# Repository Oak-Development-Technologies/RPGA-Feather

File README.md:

<image src="/images/RPGA_Feather_Banner.jpeg">

# RPGA-Feather

Welcome to the RPGA Feather GitHub page. This page is designed to be a single source of truth for this board, including board files like schematics, production files, BOM, and more. In addition to that, there are also a handful of examples available to build with just a little effort specifically for the RPGA Feather.

Continue reading to get started.

# Getting Started

What is the RPGA Feather? RPGA Feather is a development board which provides the ease of use of the RP2040 from Raspberry Pi with the wide open source support of the iCE40 FPGA line. RPGA Feather combines the RP2040 with an iCE5LP4K FPGA from Lattice Semiconductor which has 3520 LUTs, 2 hardware SPI and I2C blocks, a bright RGB LED driver, two internal oscillators, and 1 PLL which can be used to generate additional clocks for your designs.

RPGA Feather provides up to 11 direct GPIO connected between the RP2040 and the iCE5LP4K. This includes the 3 pins used for programming the bitstream onto the FPGA.

Having a good pinout guide can be useful for getting started. We provide this pinout card with every RPGA Feather purchased from our shop.

<image src="/images/RPGA%20Feather%20rev%20b.jpg">

You can find the PDF under the [Hardware Directory Here](/hardware/RPGA.pdf). Thanks to [@skliffmueller](https://github.com/skliffmueller) for making and sharing it.

### usage examples

We provide a few examples in this repository for getting familiar with interfacing with the iCE5LP4K FPGA.

Following the comments in the [top.v](/src/top.v) file under the `src` directory can enable you to build these specific examples quickly. Once you have the example set up in the file, you can build it using the following command:

```make
make build
```

Building requires using Yosys OSS CAD Suite, which can be found by visiting the [OSS CAD Suite build github repository](https://github.com/YosysHQ/oss-cad-suite-build). Follow the instructions for setting up the tools on your OS and you'll be good to go.

Once you have a `top.bin` file which should be in the base directory of the repository, you can simply copy it over onto your RPGA Feather `CIRCUITPY` drive. If you haven't downloaded the CircuitPython Community Bundle to get IcePython you can [head to the CircuitPython Libraries page](https://circuitpython.org/libraries) to download it, or [download the latest release directly](https://github.com/skerr92/Oakdevtech_CircuitPython_IcePython/releases).

Once you have IcePython and the `top.bin` file loaded onto your RPGA Feather, the next step is to get your code setup to load the FPGA.

Using Mu or your favorite CircuitPython compatible IDE, open up the `code.py` file and past the following code:

```py
# SPDX-FileCopyrightText: 2017 Scott Shawcroft, written for Adafruit Industries
# SPDX-FileCopyrightText: Copyright (c) 2023 Seth Kerr for Oak Development Technologies
#
# SPDX-License-Identifier: Unlicense

"""
Example showing how to program an iCE40 FPGA with circuitpython!
"""

import time
import board, busio
import oakdevtech_icepython
import gc

print("Mem Free: ",gc.mem_free(),"Mem Alloc", gc.mem_alloc())
spi = busio.SPI(clock=board.F_SCK, MOSI=board.F_MOSI, MISO=board.F_MISO)

iceprog = oakdevtech_icepython.Oakdevtech_icepython(
    spi, board.F_CSN, board.F_RST, "top.bin"
)

timestamp = time.monotonic()

iceprog.program_fpga()

endstamp = time.monotonic()
print("done in: ", (endstamp - timestamp), "seconds")

print("done")
```
Save the file and you should see the green CDONE LED light up on your board. Depending on the example you built, you might see the RGB LED light up that is next to the FPGA.

### Questions?

If you have any questions, please feel free to open an issue. Issues are a great way to raise concerns or bugs with the examples or hardware itself. And your feedback is critical to making sure we can fix issues and improve the quality of life for everyone's experience with RPGA Feather.

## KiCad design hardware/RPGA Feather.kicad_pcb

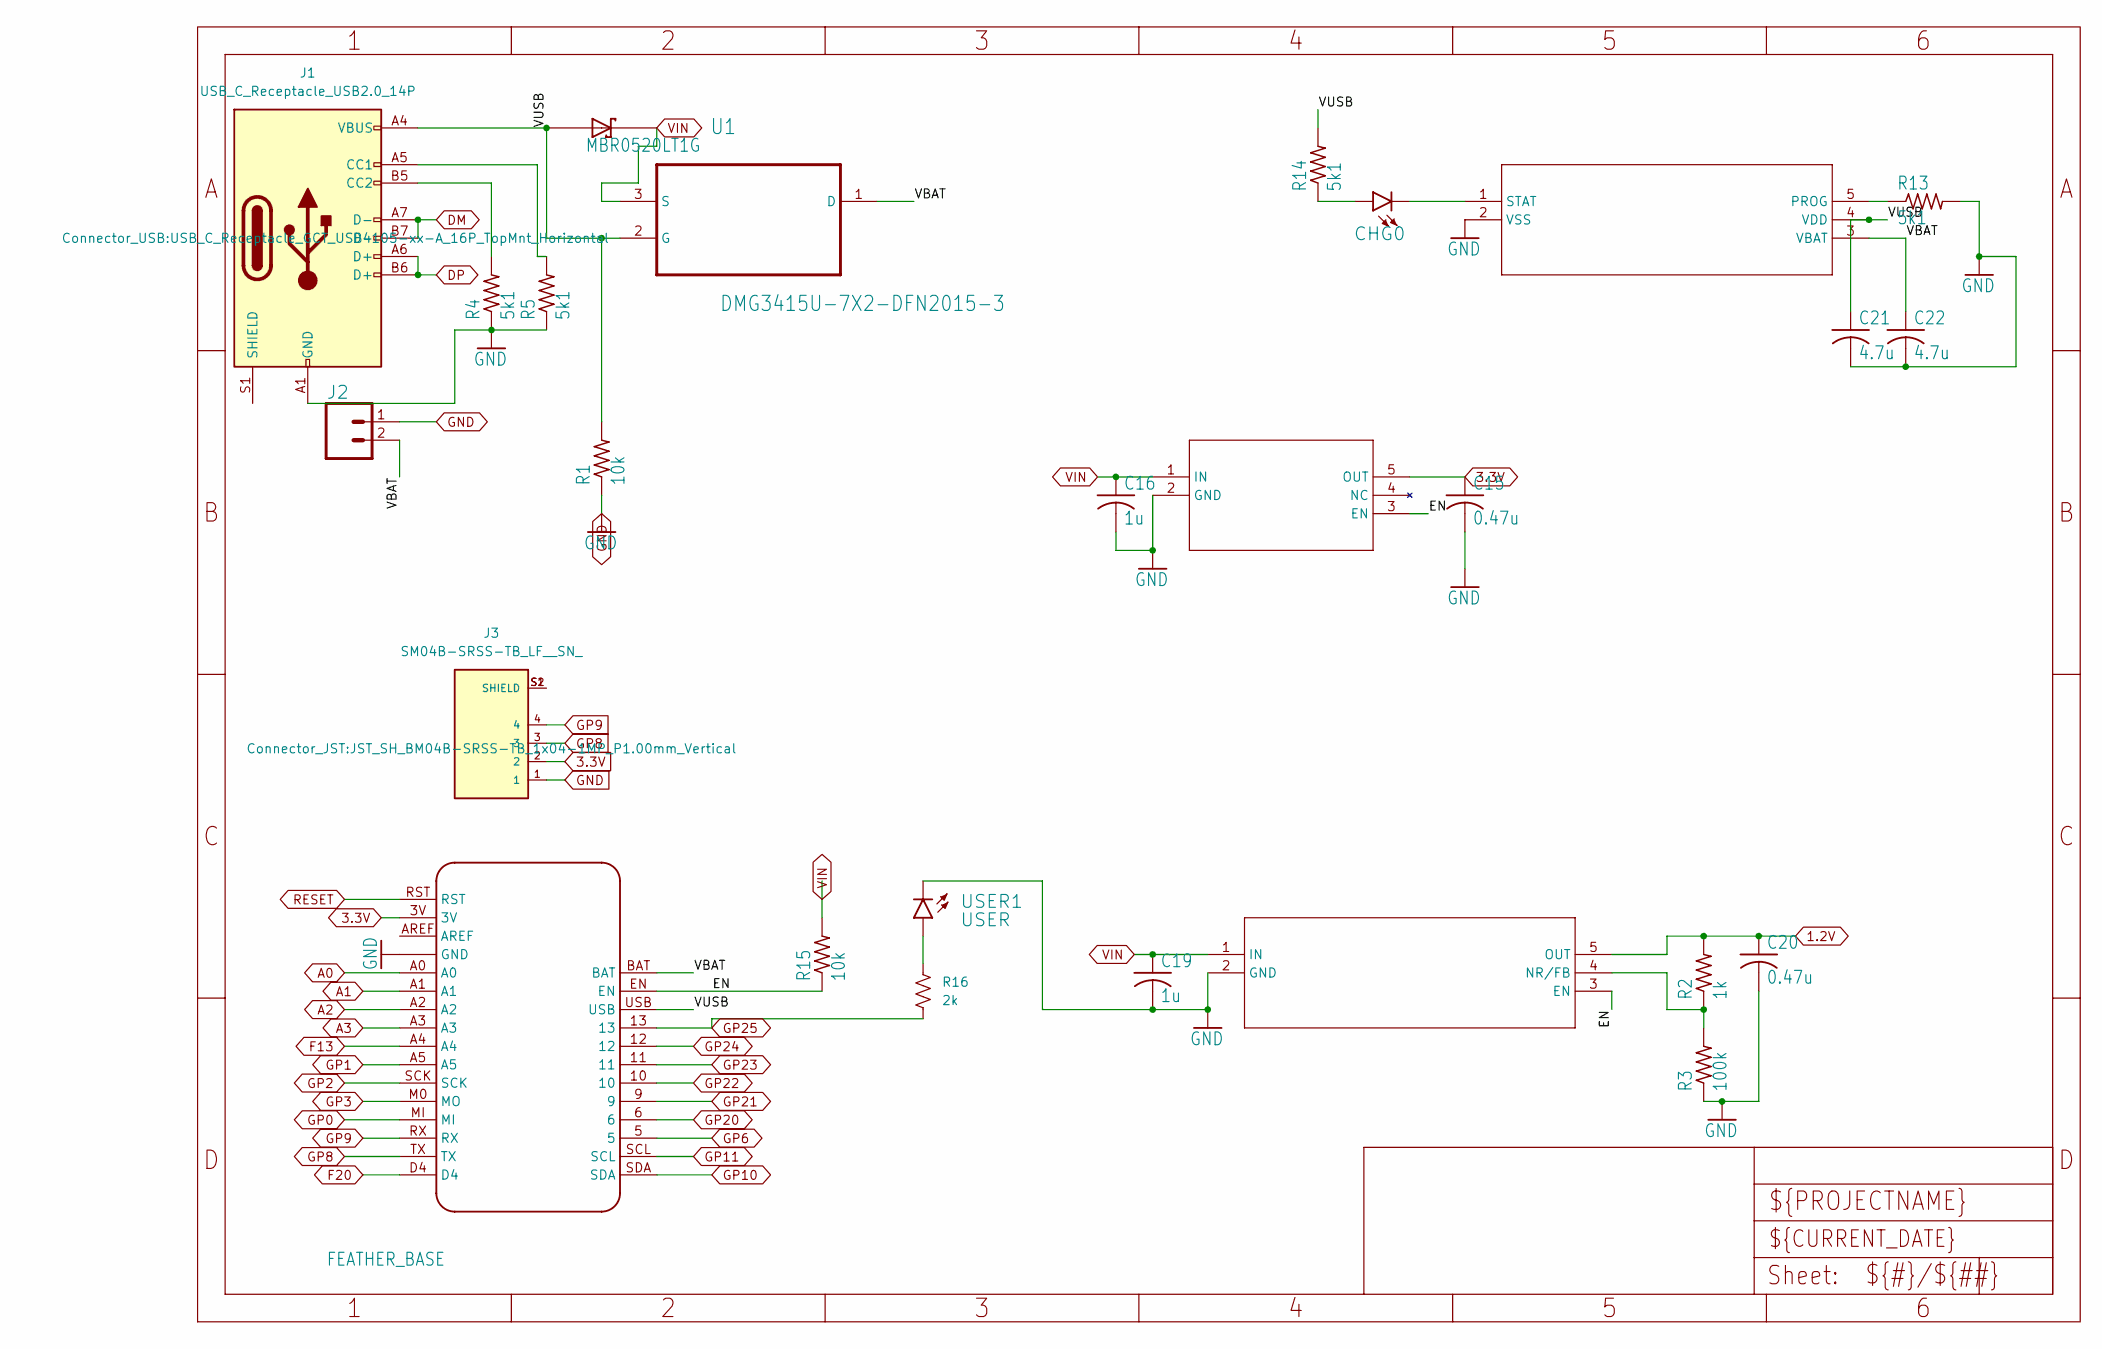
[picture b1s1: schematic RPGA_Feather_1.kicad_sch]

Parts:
C15, C20: 0.47u; C_0402_1005Metric
C16, C19: 1u; C_0402_1005Metric
C21, C22: 4.7u; C_0603_1608Metric
CHG0: LED0603; LED-0603
J1: USB_C_Receptacle_USB2.0_14P; USB_C_Receptacle_GCT_USB4105-xx-A_16P_TopMnt_Horizontal
J2: CONN_02-JST-2MM-SMT; JST-2-SMD
J3: SM04B-SRSS-TB_LF__SN_; JST_SH_BM04B-SRSS-TB_1x04-1MP_P1.00mm_Vertical
R1, R15: 10k; R0402
R2: 1k; R0402
R3: 100k; R0402
R4, R5, R13, R14: 5k1; R0402
R16: 2k; R_0402_1005Metric
U1: DMG3415U-7X2-DFN2015-3; X2-DFN2015-3
U2: MCP73831T-2ACI/OTSOT-23-5_MC-L; SOT-23-5_MC-L
U3: TPS73201DBVRDBV5-L; DBV5-L
U4: TLV75533PDBVRDBV5_TEX-L; DBV5_TEX-L
U$1: FEATHER_BASE; FEATHER_PINS
U$2: MBR0520LT1G; SOD3716X117(SOD-123)
USER1: USER; LED-0603

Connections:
1.2V: C20.1, R2.2, U3.5 (OUT); also elsewhere on the board
3.3V: C15.1, J3.2, U4.5 (OUT), U$1.3V; also elsewhere on the board
/RPGA Feather_1/EN: R15.1, U3.3 (EN), U4.3 (EN), U$1.EN
/RPGA Feather_1/VBAT: C22.1, J2.2 (1), U1.1 (D), U2.3 (VBAT), U$1.BAT
/RPGA Feather_1/VUSB: C21.1, J1.A4 (VBUS), J1.A9 (VBUS), J1.B4 (VBUS), J1.B9 (VBUS), R1.2, R14.2, U1.2 (G), U2.4 (VDD), U$1.USB, U$2.2 (A)
A0: U$1.A0; also elsewhere on the board
A1: U$1.A1; also elsewhere on the board
A2: U$1.A2; also elsewhere on the board
A3: U$1.A3; also elsewhere on the board
DM: J1.A7 (D-), J1.B7 (D-); also elsewhere on the board
DP: J1.A6 (D+), J1.B6 (D+); also elsewhere on the board
F13: U$1.A4; also elsewhere on the board
F20: U$1.D4; also elsewhere on the board
GND: C15.2, C16.2, C19.2, C20.2, C21.2, C22.2, J1.A1 (GND), J1.A12 (GND), J1.B1 (GND), J1.B12 (GND), J2.1 (2), J3.1, R1.1, R3.1, R4.1, R5.1, R13.2, U2.2 (VSS), U3.2 (GND), U4.2 (GND), U$1.GND, U$1.P$1 (GND), U$1.P$2 (GND), USER1.C; also elsewhere on the board
GP0: U$1.MI; also elsewhere on the board
GP1: U$1.A5; also elsewhere on the board
GP2: U$1.SCK; also elsewhere on the board
GP3: U$1.M0 (MO); also elsewhere on the board
GP6: U$1.5; also elsewhere on the board
GP8: J3.3, U$1.TX; also elsewhere on the board
GP9: J3.4, U$1.RX; also elsewhere on the board
GP10: U$1.SDA; also elsewhere on the board
GP11: U$1.SCL; also elsewhere on the board
GP20: U$1.6; also elsewhere on the board
GP21: U$1.9; also elsewhere on the board
GP22: U$1.10; also elsewhere on the board
GP23: U$1.11; also elsewhere on the board
GP24: U$1.12; also elsewhere on the board
GP25: R16.2, U$1.13; also elsewhere on the board
unnamed: CHG0.A, R14.1
unnamed: J1.A5 (CC1), R5.2
unnamed: J1.B5 (CC2), R4.2
unnamed: R16.1, USER1.A
unnamed: R13.1, U2.5 (PROG)
unnamed: CHG0.C, U2.1 (STAT)
unnamed: R2.1, R3.2, U3.4 (NR/FB)
RESET: U$1.RST; also elsewhere on the board
VIN: C16.1, C19.1, R15.2, U1.3 (S), U3.1 (IN), U4.1 (IN), U$2.1 (C)

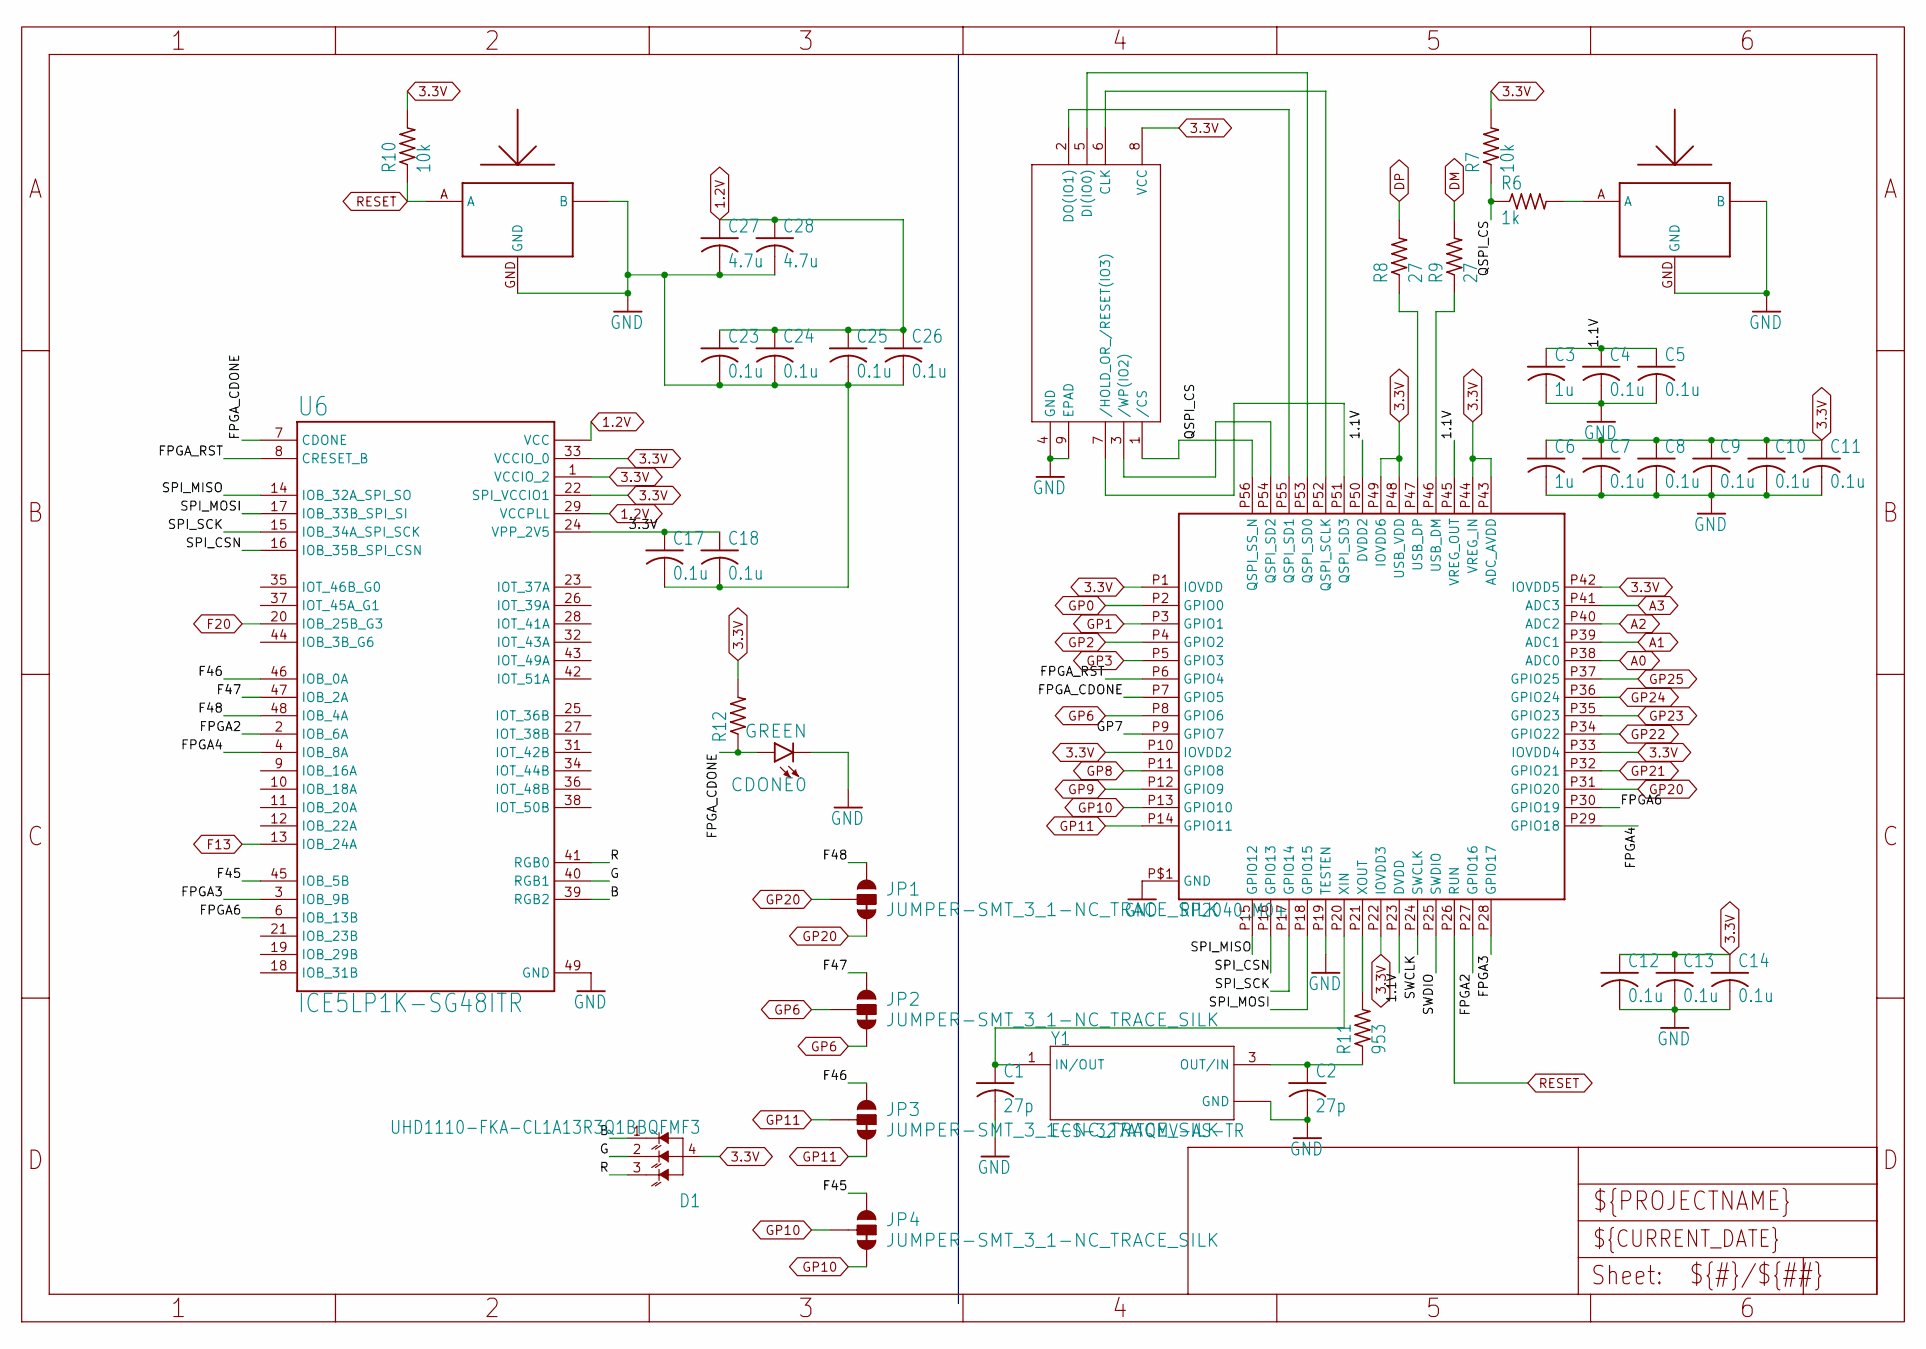
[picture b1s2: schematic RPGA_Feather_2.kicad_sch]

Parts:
C1, C2: 27p; C_0402_1005Metric
C3, C6: 1u; C_0402_1005Metric
C4, C5, C7, C8, C9, C10, C11, C12, C13, C14, C17, C18, C23, C24, C25, C26: 0.1u; C_0402_1005Metric
C27, C28: 4.7u; C_0603_1608Metric
CDONE0: GREEN; LED-0603
D1: UHD1110-FKA-CL1A13R3Q1BBQFMF3; LED_UHD1110-FKA-CL1A13R3Q1BBQFMF3
JP1, JP2, JP3, JP4: JUMPER-SMT_3_1-NC_TRACE_SILK; SMT-JUMPER_3_1-NC_TRACE_SILK
R6: 1k; R0402
R7, R10: 10k; R0402
R8, R9: 27; R0402
R11: 953; R0402
R12: R-US_R0402; R0402
U6: ICE5LP1K-SG48ITR; QFN50P700X700X100-49N
U7: W25Q16JVUXIQW25Q16JVUXIQ_WIN-L; W25Q16JVUXIQ_WIN-L
U$3: RP2040_M0+; QFN-56
U$4, U$5: SOF-232HST; 3.3X2.9
Y1: ECS-327ATQMV-AS-TR; XTAL_ECS-327ATQMV-AS-TR

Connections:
1.2V: C23.1, C24.1, C25.1, C26.1, C27.1, C28.1, U6.5 (VCC), U6.29 (VCCPLL), U6.30 (VCC); also elsewhere on the board
3.3V: C6.1, C7.1, C8.1, C9.1, C10.1, C11.1, C12.1, C13.1, C14.1, C17.1, C18.1, D1.4 (ANODE), R7.2, R10.2, R12.2, U6.1 (VCCIO_2), U6.22 (SPI_VCCIO1), U6.24 (VPP_2V5), U6.33 (VCCIO_0), U7.8 (VCC), U$3.P1 (IOVDD), U$3.P10 (IOVDD2), U$3.P22 (IOVDD3), U$3.P33 (IOVDD4), U$3.P42 (IOVDD5), U$3.P43 (ADC_AVDD), U$3.P44 (VREG_IN), U$3.P48 (USB_VDD), U$3.P49 (IOVDD6); also elsewhere on the board
/RPGA Feather_2/1.1V: C3.1, C4.1, C5.1, U$3.P23 (DVDD), U$3.P45 (VREG_OUT), U$3.P50 (DVDD2)
/RPGA Feather_2/B: D1.1 (BLUE), U6.39 (RGB2)
/RPGA Feather_2/F45: JP4.1, U6.45 (IOB_5B)
/RPGA Feather_2/F46: JP3.1, U6.46 (IOB_0A)
/RPGA Feather_2/F47: JP2.1, U6.47 (IOB_2A)
/RPGA Feather_2/F48: JP1.1, U6.48 (IOB_4A)
/RPGA Feather_2/FPGA2: U6.2 (IOB_6A), U$3.P27 (GPIO16)
/RPGA Feather_2/FPGA3: U6.3 (IOB_9B), U$3.P28 (GPIO17)
/RPGA Feather_2/FPGA4: U6.4 (IOB_8A), U$3.P29 (GPIO18)
/RPGA Feather_2/FPGA6: U6.6 (IOB_13B), U$3.P30 (GPIO19)
/RPGA Feather_2/FPGA_CDONE: CDONE0.A, R12.1, U6.7 (CDONE), U$3.P7 (GPIO5)
/RPGA Feather_2/FPGA_RST: U6.8 (CRESET_B), U$3.P6 (GPIO4)
/RPGA Feather_2/G: D1.2 (GREEN), U6.40 (RGB1)
/RPGA Feather_2/GP7: U$3.P9 (GPIO7)
/RPGA Feather_2/QSPI_CS: R6.1, R7.1, U7.1 (/CS), U$3.P56 (QSPI_SS_N)
/RPGA Feather_2/R: D1.3 (RED), U6.41 (RGB0)
/RPGA Feather_2/SPI_CSN: U6.16 (IOB_35B_SPI_CSN), U$3.P16 (GPIO13)
/RPGA Feather_2/SPI_MISO: U6.14 (IOB_32A_SPI_SO), U$3.P15 (GPIO12)
/RPGA Feather_2/SPI_MOSI: U6.17 (IOB_33B_SPI_SI), U$3.P18 (GPIO15)
/RPGA Feather_2/SPI_SCK: U6.15 (IOB_34A_SPI_SCK), U$3.P17 (GPIO14)
/RPGA Feather_2/SWCLK: U$3.P24 (SWCLK)
/RPGA Feather_2/SWDIO: U$3.P25 (SWDIO)
A0: U$3.P38 (ADC0); also elsewhere on the board
A1: U$3.P39 (ADC1); also elsewhere on the board
A2: U$3.P40 (ADC2); also elsewhere on the board
A3: U$3.P41 (ADC3); also elsewhere on the board
DM: R9.2; also elsewhere on the board
DP: R8.2; also elsewhere on the board
F13: U6.13 (IOB_24A); also elsewhere on the board
F20: U6.20 (IOB_25B_G3); also elsewhere on the board
GND: C1.2, C2.2, C3.2, C4.2, C5.2, C6.2, C7.2, C8.2, C9.2, C10.2, C11.2, C12.2, C13.2, C14.2, C17.2, C18.2, C23.2, C24.2, C25.2, C26.2, C27.2, C28.2, CDONE0.C, U6.49 (GND), U7.4 (GND), U7.9 (EPAD), U$3.P19 (TESTEN), U$3.P$1 (GND), U$4.B, U$4.B2 (B), U$4.B3 (B), U$4.GND, U$5.B, U$5.B2 (B), U$5.B3 (B), U$5.GND, Y1.2 (GND), Y1.4 (GND); also elsewhere on the board
GP0: U$3.P2 (GPIO0); also elsewhere on the board
GP1: U$3.P3 (GPIO1); also elsewhere on the board
GP2: U$3.P4 (GPIO2); also elsewhere on the board
GP3: U$3.P5 (GPIO3); also elsewhere on the board
GP6: JP2.2, JP2.3, U$3.P8 (GPIO6); also elsewhere on the board
GP8: U$3.P11 (GPIO8); also elsewhere on the board
GP9: U$3.P12 (GPIO9); also elsewhere on the board
GP10: JP4.2, JP4.3, U$3.P13 (GPIO10); also elsewhere on the board
GP11: JP3.2, JP3.3, U$3.P14 (GPIO11); also elsewhere on the board
GP20: JP1.2, JP1.3, U$3.P31 (GPIO20); also elsewhere on the board
GP21: U$3.P32 (GPIO21); also elsewhere on the board
GP22: U$3.P34 (GPIO22); also elsewhere on the board
GP23: U$3.P35 (GPIO23); also elsewhere on the board
GP24: U$3.P36 (GPIO24); also elsewhere on the board
GP25: U$3.P37 (GPIO25); also elsewhere on the board
unnamed: R6.2, U$5.A
unnamed: U7.6 (CLK), U$3.P52 (QSPI_SCLK)
unnamed: U7.5 (DI(IO0)), U$3.P53 (QSPI_SD0)
unnamed: U7.2 (DO(IO1)), U$3.P55 (QSPI_SD1)
unnamed: U7.3 (/WP(IO2)), U$3.P54 (QSPI_SD2)
unnamed: U7.7 (/HOLD_OR_/RESET(IO3)), U$3.P51 (QSPI_SD3)
unnamed: R9.1, U$3.P46 (USB_DM)
unnamed: R8.1, U$3.P47 (USB_DP)
unnamed: C1.1, U$3.P20 (XIN), Y1.1 (IN/OUT)
unnamed: R11.2, U$3.P21 (XOUT)
unnamed: C2.1, R11.1, Y1.3 (OUT/IN)
RESET: R10.1, U$3.P26 (RUN), U$4.A; also elsewhere on the board

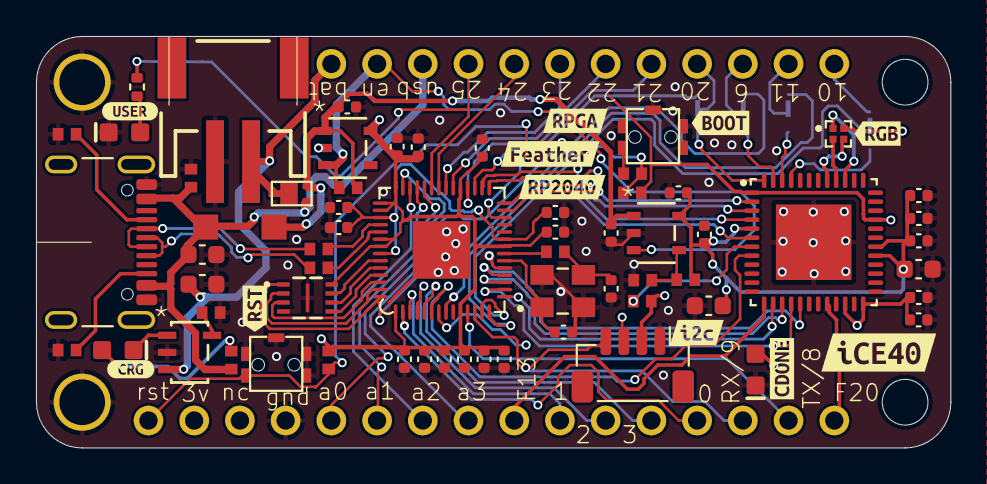
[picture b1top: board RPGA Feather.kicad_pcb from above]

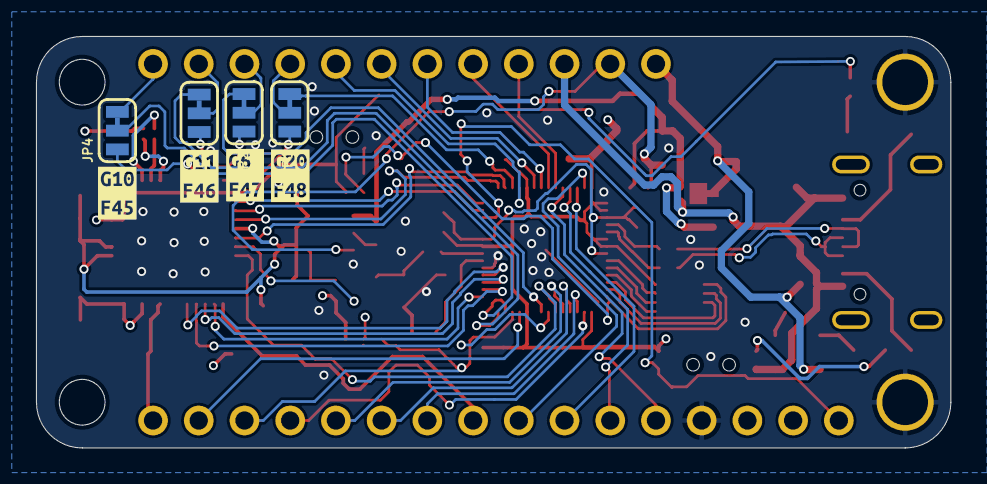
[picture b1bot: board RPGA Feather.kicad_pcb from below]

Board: 4 copper layers, 50.8 x 22.9 mm, 82 parts (8 on the bottom side), 68 nets.

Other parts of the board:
kibuzzard-6601CD6F: G***; kibuzzard-6601CD6F
kibuzzard-6601CD49: G***; kibuzzard-6601CD49
kibuzzard-6601CDB5: G***; kibuzzard-6601CDB5
kibuzzard-6601CDBD: G***; kibuzzard-6601CDBD
kibuzzard-6601FC5E: G***; kibuzzard-6601FC5E
kibuzzard-6601FC9E: G***; kibuzzard-6601FC9E
kibuzzard-6601FC47: G***; kibuzzard-6601FC47
kibuzzard-6601FCCE: G***; kibuzzard-6601FCCE
kibuzzard-6601FCEA: G***; kibuzzard-6601FCEA
kibuzzard-6601FCFE: G***; kibuzzard-6601FCFE
kibuzzard-6601FD10: G***; kibuzzard-6601FD10
kibuzzard-66565BE9: G***; kibuzzard-66565BE9
kibuzzard-660226BE: G***; kibuzzard-660226BE
kibuzzard-6657261C: G***; kibuzzard-6657261C
kibuzzard-66022711: G***; kibuzzard-66022711

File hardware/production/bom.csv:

Designator,Footprint,Quantity,Value,LCSC Part #
"C1, C2",0402,2,27p,
"C10, C11, C12, C13, C14, C17, C18, C23, C24, C25, C26, C4, C5, C7, C8, C9",0402,16,0.1u,
"C15, C20",0402,2,0.47u,
"C16, C19, C3, C6",0402,4,1u,
"C21, C22, C27, C28",0603,4,4.7u,
CDONE0,LED-0603,1,GREEN,
CHG0,LED-0603,1,LED0603,
D1,LED_UHD1110-FKA-CL1A13R3Q1BBQFMF3,1,UHD1110-FKA-CL1A13R3Q1BBQFMF3,
J1,USB_C_Receptacle_GCT_USB4105-xx-A_16P_TopMnt_Horizontal,1,USB_C_Receptacle_USB2.0_14P,
J2,JST-2-SMD,1,CONN_02-JST-2MM-SMT,
J3,JST_SH_BM04B-SRSS-TB_1x04-1MP_P1.00mm_Vertical,1,SM04B-SRSS-TB_LF__SN_,
"JP1, JP2, JP3, JP4",SMT-JUMPER_3_1-NC_TRACE_SILK,4,JUMPER-SMT_3_1-NC_TRACE_SILK,
"R1, R10, R15, R7",R0402,4,10k,
R11,R0402,1,953,
R12,R0402,1,R-US_R0402,
"R13, R14, R4, R5",R0402,4,5k1,
R16,0402,1,2k,
"R2, R6",R0402,2,1k,
R3,R0402,1,100k,
"R8, R9",R0402,2,27,
U$1,FEATHER_PINS,1,FEATHER_BASE,
U$2,SOD3716X117(SOD-123),1,MBR0520LT1G,
U$3,QFN-56,1,RP2040_M0+,
"U$4, U$5",3.3X2.9,2,SOF-232HST,
U1,X2-DFN2015-3,1,DMG3415U-7X2-DFN2015-3,
U2,SOT-23-5_MC-L,1,MCP73831T-2ACI/OTSOT-23-5_MC-L,
U3,DBV5-L,1,TPS73201DBVRDBV5-L,
U4,DBV5_TEX-L,1,TLV75533PDBVRDBV5_TEX-L,
U6,QFN50P700X700X100-49N,1,ICE5LP1K-SG48ITR,
U7,W25Q16JVUXIQ_WIN-L,1,W25Q16JVUXIQW25Q16JVUXIQ_WIN-L,
USER1,LED-0603,1,USER,
Y1,XTAL_ECS-327ATQMV-AS-TR,1,ECS-327ATQMV-AS-TR,

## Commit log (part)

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2024-06-03 add hardware files
2024-06-07 update readme instructions
2024-06-23 fix build command for examples
2024-06-23 one other makefile fix
2024-08-10 PDF of RPGA Feather Schematic
2024-08-10 Update README.md
    add pdf of schematic
